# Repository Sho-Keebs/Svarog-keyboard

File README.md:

## ⚠ Notice

This project is no longer under active developement. If you want to work on this, please contact me @ [echelon.div@gmail.com](mailto:echelon.div@gmail.com).

# Svarog-keyboard

This is my first attempt to make mechanical keyboard. It was supposed to look little bit retro, and have as many additional keys as possible, without taking a lot of space. Additionaly it has customizable and optional sidepanels (Numerical and Navigational).

# License and availability

The whole project is released under GNU GPL v3. What does it mean? You can get fabrication files completely free of charge, modify the source files of keyboard, and even fabricate and sell it without me knowing it. What’s the catch then? You have to have few things in mind:
- There is no liability or warranty from my side that the keyboard is working (especially in current state),
- If you want to fork my project you have to use the same license.

# Firmware

The goal is to use QMK. BUT Board is untested, no one built it yet. So obviously there is no working QMK configuration for it. You might get it working while using Discipline 65 config, but you won’t be able to get all keys working (if any), as pins on ATMega32A microcontroller are wired differently between these two keyboards.

# Supported Layouts

1. Split and 2u `Backspace`,
2. 6.25u and 7u `Spacebar`
3. ISO and ANSI `Return`
4. Split and 2.25u `Left Shift`
5. Split and 2.75 `Full Shift`
6. Split and 2u `Enter (NumPad)`
7. Split and 2u `0 / Ins`
8. Split and 2u `+`

# Parts

|Part|Amount|Picture|
|---|---|---|
|ATMega32A-PU|1||
|DIP-40 15.24mm Socket|1||
|MCP23017-E/SP|3||
|DIP-28 7.62mm Socket|3||
|MX Style 5-pin Switch|124||
|Diodes 1N4148|124||
|ISP Header 02x03 2.54mm|1||
|16 MHz Crystal|1||
|6mm Push Buttons|2||
|LED 3.0mm|7||
|Electrolictic Capacitor 4.7uF|1||
|Ceramic Capacitor 22pF|2||
|Ceramic Capacitor 0.1uF|2||
|Zener Diode 3.6V|2||
|Polyfuse 500mA|1||
|Resistor 1.5k Ohm|8||
|Resistor 10k Ohm|3||
|Resistor 5.1k Ohm|2||
|Resistor 75 Ohm|2||

# Pre-Release
So as for now, I’ve published pre-release fabrication files for anyone who want to try to build and test it in it’s current form.

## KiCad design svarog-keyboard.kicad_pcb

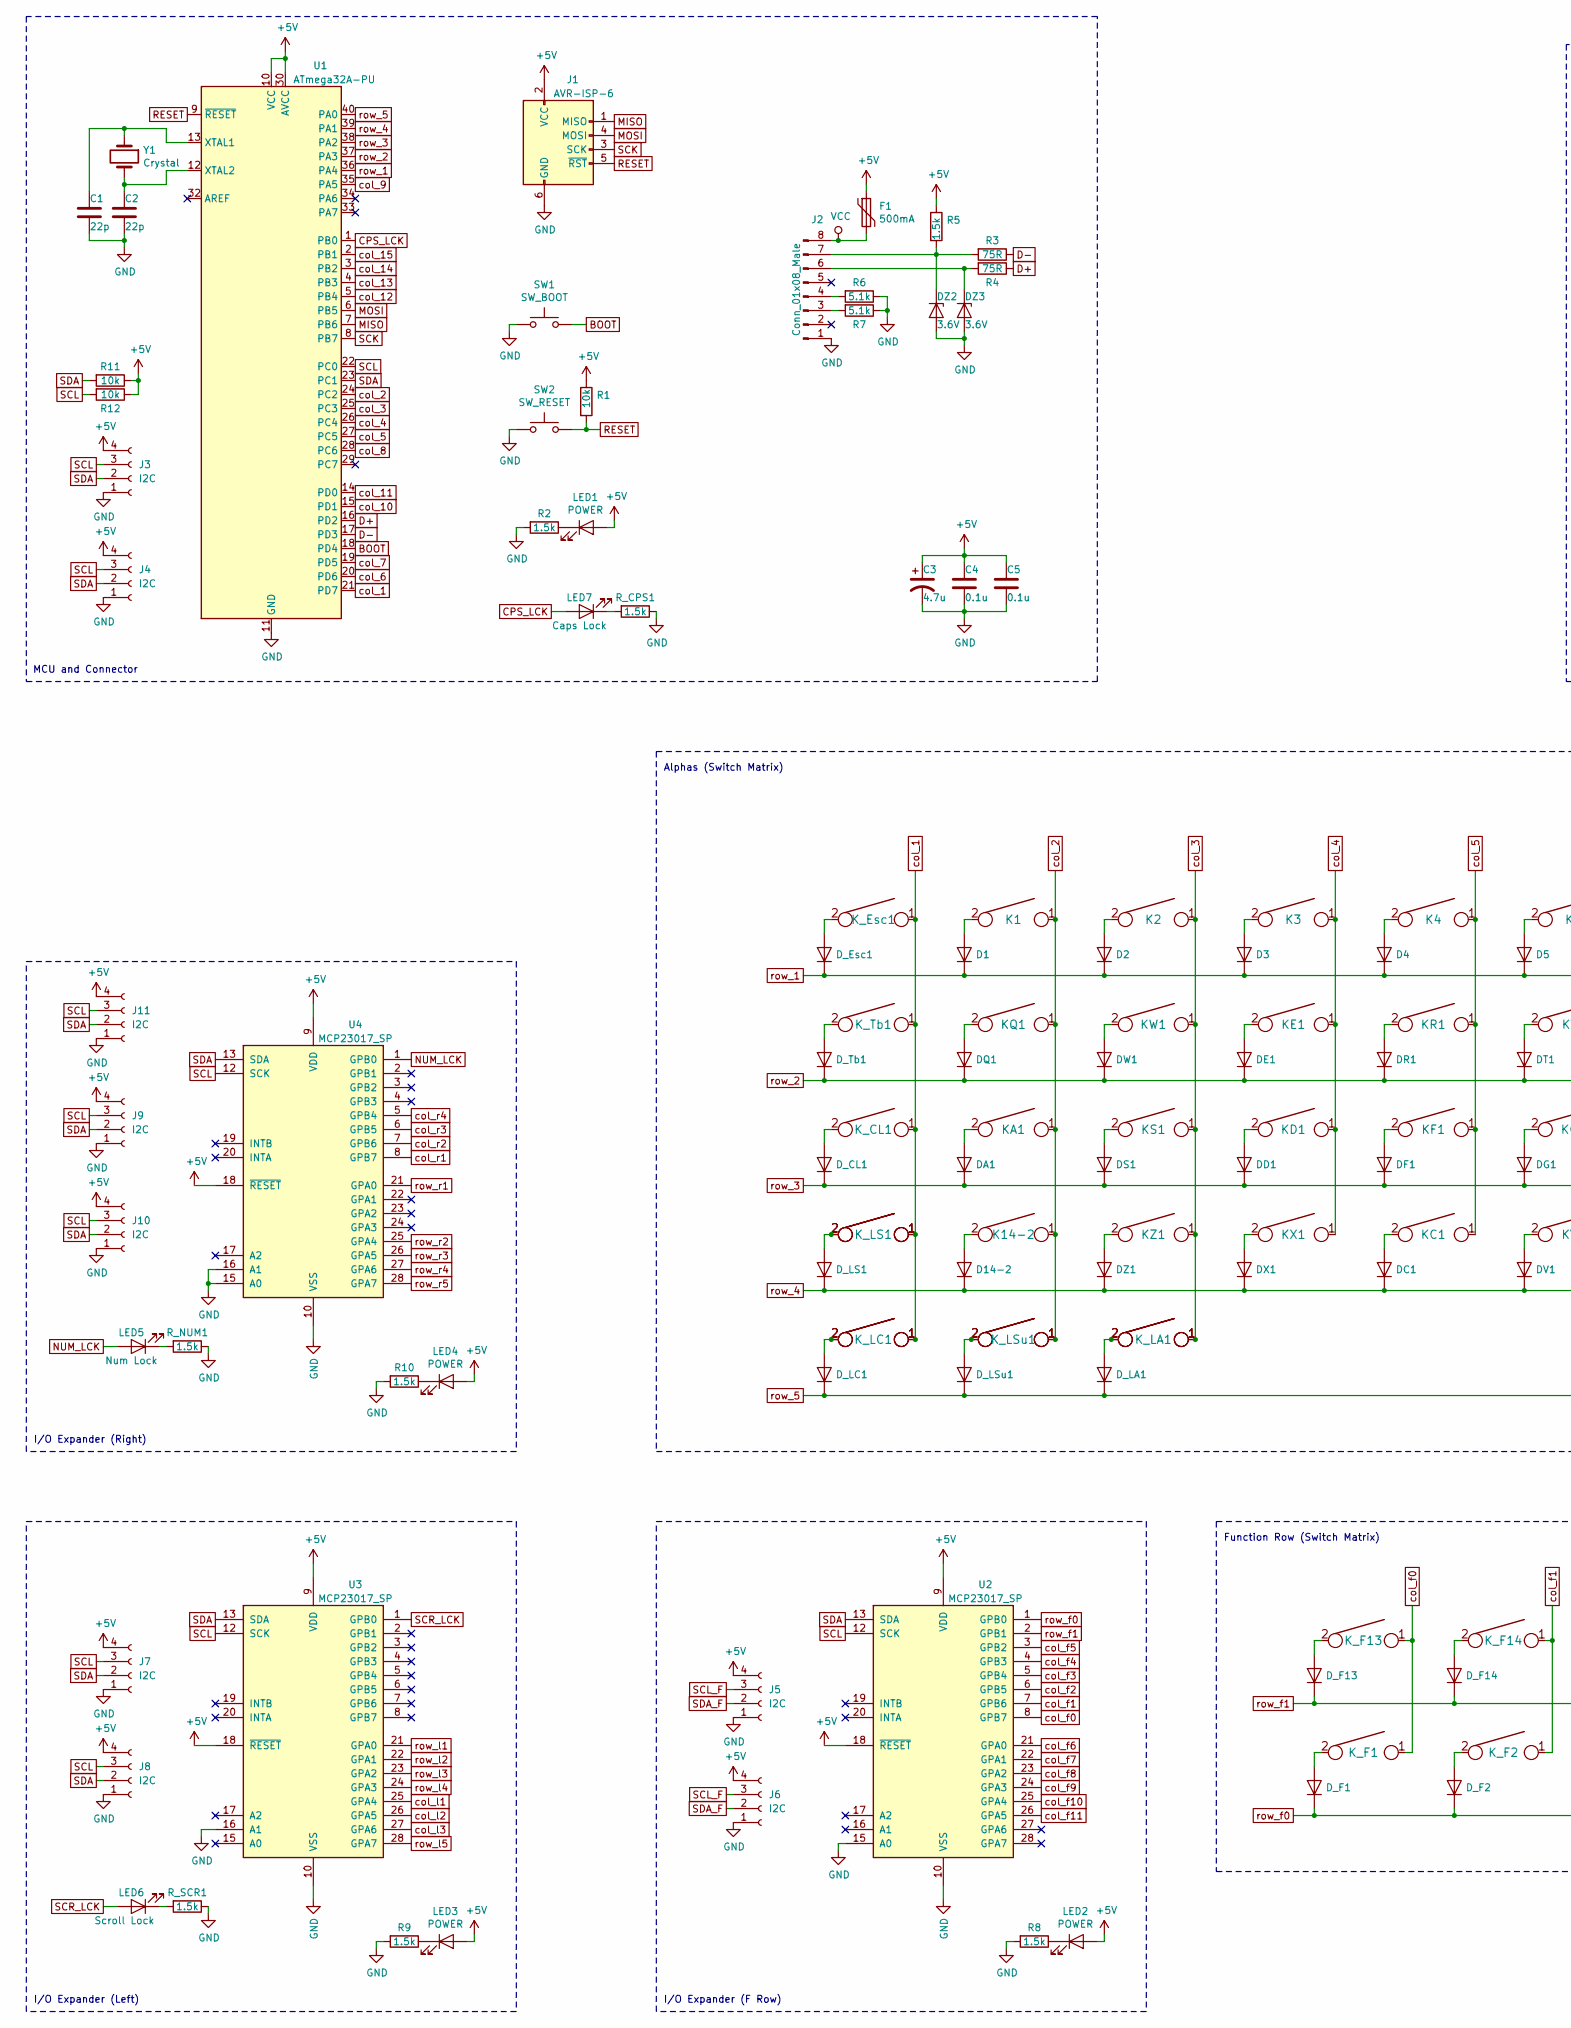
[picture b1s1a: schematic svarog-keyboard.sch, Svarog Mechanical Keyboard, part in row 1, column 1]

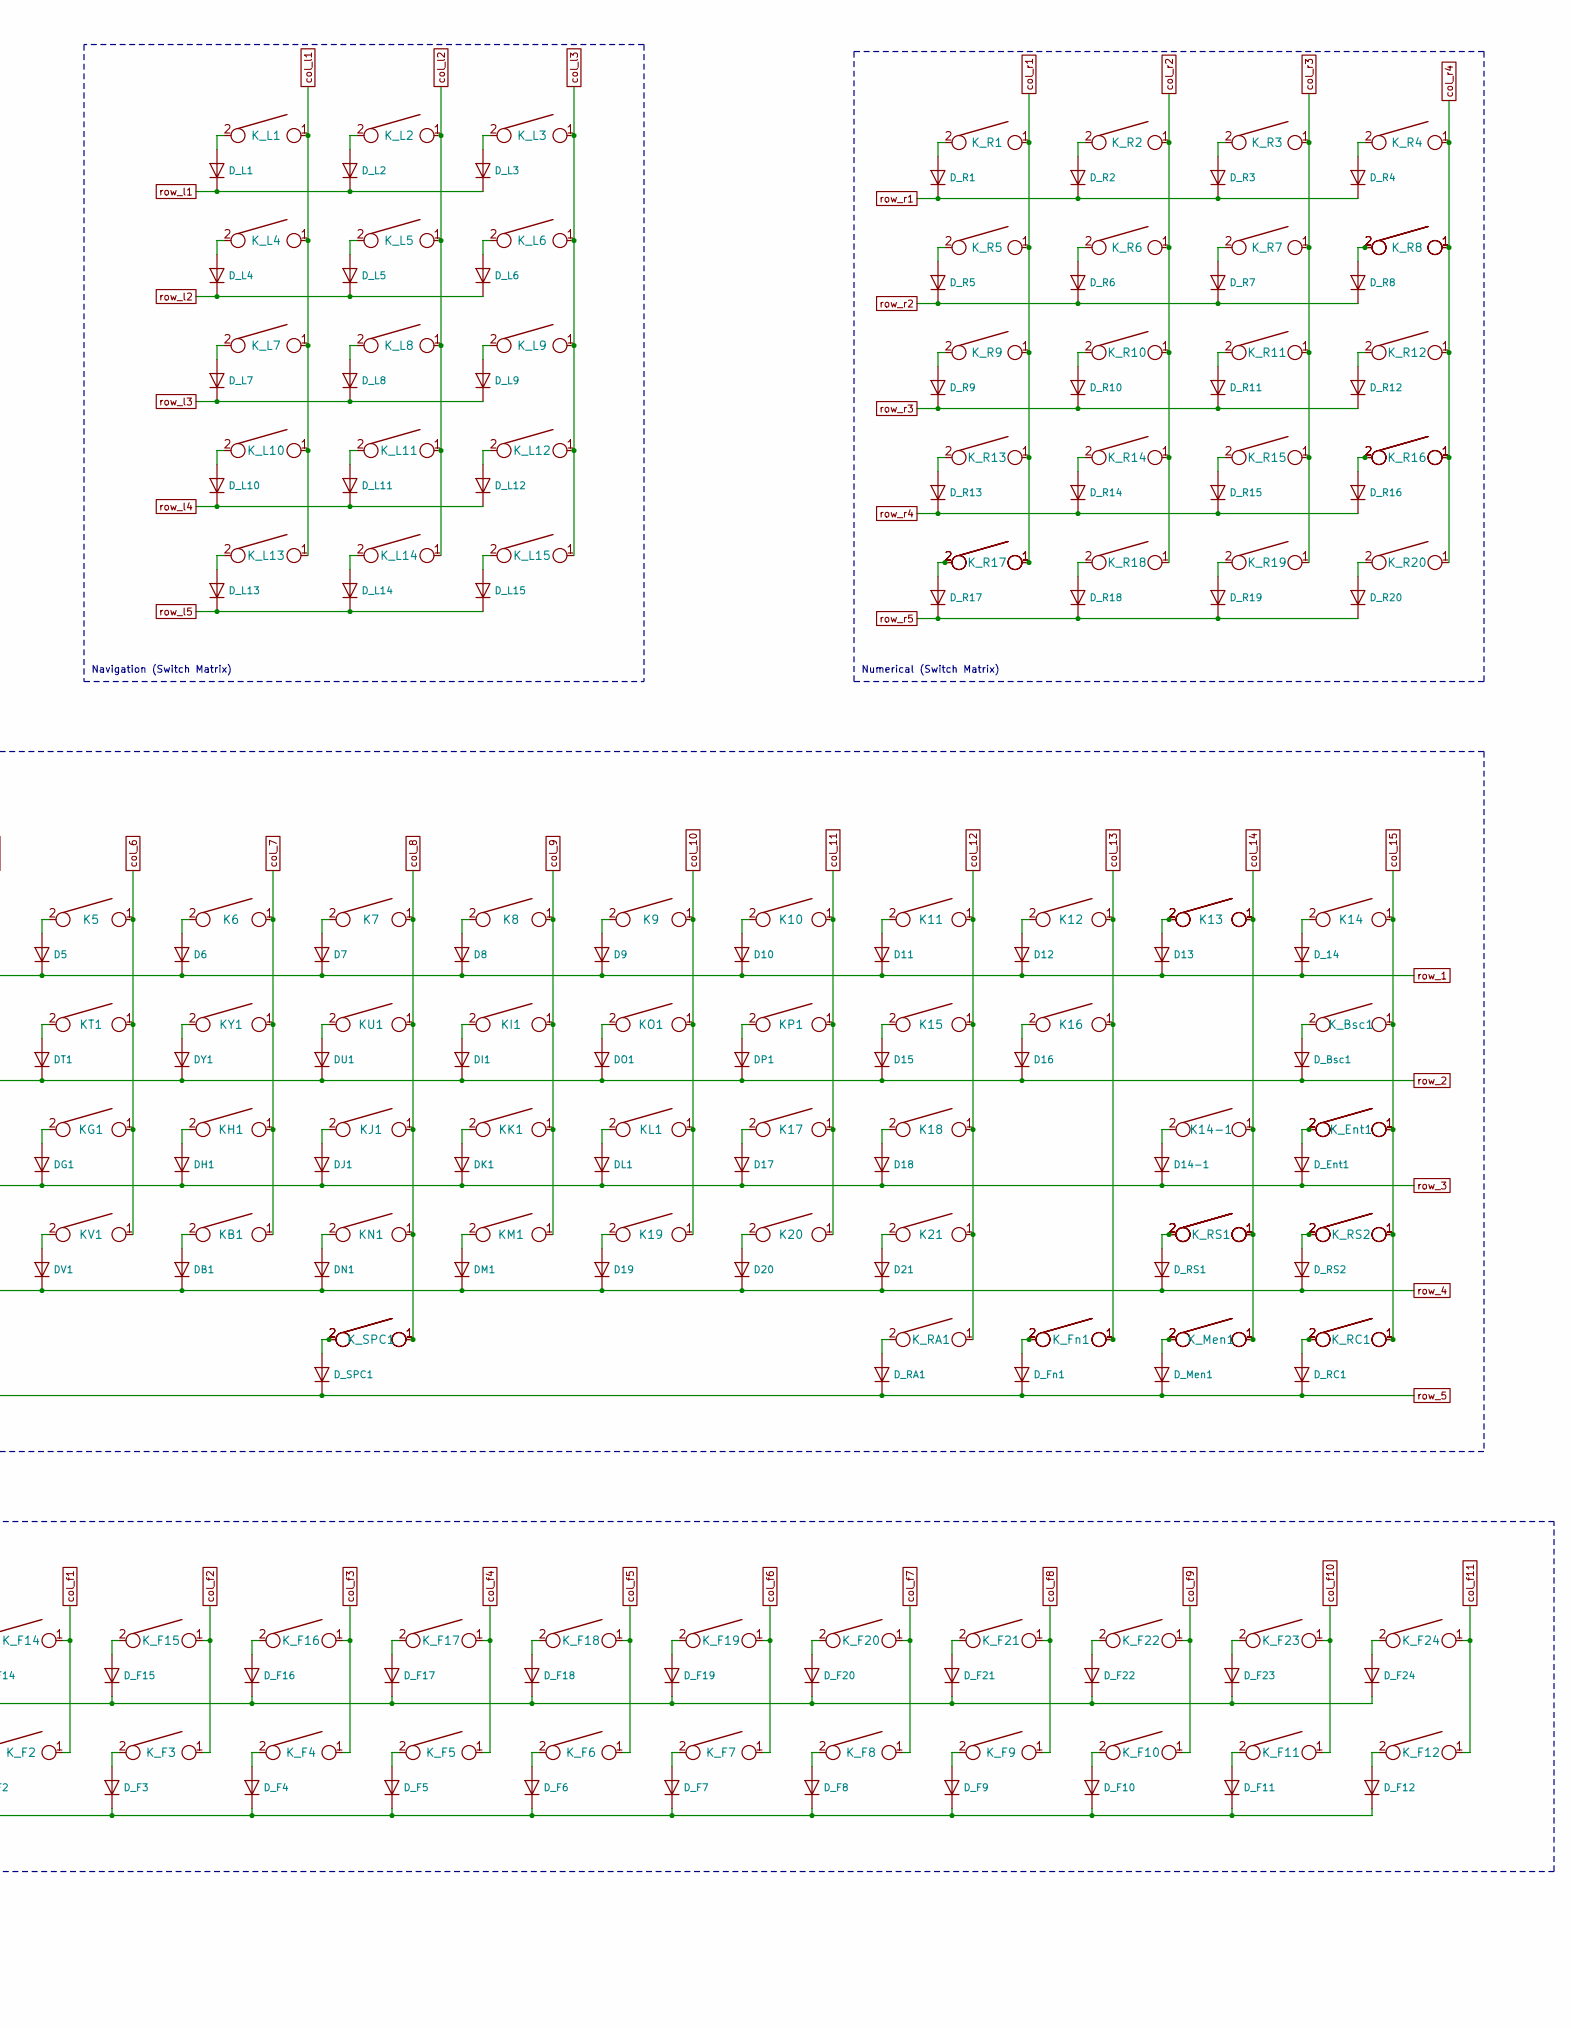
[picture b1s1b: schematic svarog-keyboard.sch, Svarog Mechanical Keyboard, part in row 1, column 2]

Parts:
C1: 22p; C_Disc_D3.4mm_W2.1mm_P2.50mm
C2: 22p; C_Disc_D3.8mm_W2.6mm_P2.50mm
C3: 4.7u; CP_Radial_D4.0mm_P1.50mm
C4, C5: 0.1u; C_Disc_D3.8mm_W2.6mm_P2.50mm
D1, D2, D3, D4, D5, D6, D7, D8, D9, D10, D11, D12, D13, D14-1, D14-2, D15, D16, D17, D18, D19, D20, D21: D; D_DO-35_SOD27_P7.62mm_Horizontal
DA1: D; D_DO-35_SOD27_P7.62mm_Horizontal
DB1: D; D_DO-35_SOD27_P7.62mm_Horizontal
DC1: D; D_DO-35_SOD27_P7.62mm_Horizontal
DD1: D; D_DO-35_SOD27_P7.62mm_Horizontal
DE1: D; D_DO-35_SOD27_P7.62mm_Horizontal
DF1: D; D_DO-35_SOD27_P7.62mm_Horizontal
DG1: D; D_DO-35_SOD27_P7.62mm_Horizontal
DH1: D; D_DO-35_SOD27_P7.62mm_Horizontal
DI1: D; D_DO-35_SOD27_P7.62mm_Horizontal
DJ1: D; D_DO-35_SOD27_P7.62mm_Horizontal
DK1: D; D_DO-35_SOD27_P7.62mm_Horizontal
DL1: D; D_DO-35_SOD27_P7.62mm_Horizontal
DM1: D; D_DO-35_SOD27_P7.62mm_Horizontal
DN1: D; D_DO-35_SOD27_P7.62mm_Horizontal
DO1: D; D_DO-35_SOD27_P7.62mm_Horizontal
DP1: D; D_DO-35_SOD27_P7.62mm_Horizontal
DQ1: D; D_DO-35_SOD27_P7.62mm_Horizontal
DR1: D; D_DO-35_SOD27_P7.62mm_Horizontal
DS1: D; D_DO-35_SOD27_P7.62mm_Horizontal
DT1: D; D_DO-35_SOD27_P7.62mm_Horizontal
DU1: D; D_DO-35_SOD27_P7.62mm_Horizontal
DV1: D; D_DO-35_SOD27_P7.62mm_Horizontal
DW1: D; D_DO-35_SOD27_P7.62mm_Horizontal
DX1: D; D_DO-35_SOD27_P7.62mm_Horizontal
DY1: D; D_DO-35_SOD27_P7.62mm_Horizontal
DZ1: D; D_DO-35_SOD27_P7.62mm_Horizontal
DZ2, DZ3: 3.6V; D_DO-35_SOD27_P7.62mm_Horizontal
D_14: D; D_DO-35_SOD27_P7.62mm_Horizontal
D_Bsc1: D; D_DO-35_SOD27_P7.62mm_Horizontal
D_CL1: D; D_DO-35_SOD27_P7.62mm_Horizontal
D_Ent1: D; D_DO-35_SOD27_P7.62mm_Horizontal
D_Esc1: D; D_DO-35_SOD27_P7.62mm_Horizontal
D_F1, D_F2, D_F3, D_F4, D_F5, D_F6, D_F7, D_F8, D_F9, D_F10, D_F11, D_F12, D_F13, D_F14, D_F15, D_F16, D_F17, D_F18, D_F19, D_F20, D_F21, D_F22, D_F23, D_F24: D; D_DO-35_SOD27_P7.62mm_Horizontal
D_Fn1: D; D_DO-35_SOD27_P7.62mm_Horizontal
D_L1, D_L2, D_L3, D_L4, D_L5, D_L6, D_L7, D_L8, D_L9, D_L10, D_L11, D_L12, D_L13, D_L14, D_L15: D; D_DO-35_SOD27_P7.62mm_Horizontal
D_LA1: D; D_DO-35_SOD27_P7.62mm_Horizontal
D_LC1: D; D_DO-35_SOD27_P7.62mm_Horizontal
D_LS1: D; D_DO-35_SOD27_P7.62mm_Horizontal
D_LSu1: D; D_DO-35_SOD27_P7.62mm_Horizontal
D_Men1: D; D_DO-35_SOD27_P7.62mm_Horizontal
D_R1, D_R2, D_R3, D_R4, D_R5, D_R6, D_R7, D_R8, D_R9, D_R10, D_R11, D_R12, D_R13, D_R14, D_R15, D_R16, D_R17, D_R18, D_R19, D_R20: D; D_DO-35_SOD27_P7.62mm_Horizontal
D_RA1: D; D_DO-35_SOD27_P7.62mm_Horizontal
D_RC1: D; D_DO-35_SOD27_P7.62mm_Horizontal
D_RS1, D_RS2: D; D_DO-35_SOD27_P7.62mm_Horizontal
D_SPC1: D; D_DO-35_SOD27_P7.62mm_Horizontal
D_Tb1: D; D_DO-35_SOD27_P7.62mm_Horizontal
F1: 500mA; C_Disc_D9.0mm_W5.0mm_P10.00mm
J1: AVR-ISP-6; PinHeader_2x03_P2.54mm_Vertical
J2: Conn_01x08_Male; PinHeader_1x08_P2.54mm_Vertical
J3, J4, J5, J6, J7, J8, J9, J10, J11: I2C; PinHeader_1x04_P2.54mm_Vertical
K1, K2, K3, K4, K5, K6, K7, K8, K9, K10, K11, K12, K13, K14, K14-1, K14-2, K15, K16, K17, K18, K19, K20, K21: KEYSW; SW_Cherry_MX_1.00u_PCB
K13-1: KEYSW; SW_Cherry_MX_2.00u_PCB
KA1: KEYSW; SW_Cherry_MX_1.00u_PCB
KB1: KEYSW; SW_Cherry_MX_1.00u_PCB
KC1: KEYSW; SW_Cherry_MX_1.00u_PCB
KD1: KEYSW; SW_Cherry_MX_1.00u_PCB
KE1: KEYSW; SW_Cherry_MX_1.00u_PCB
KF1: KEYSW; SW_Cherry_MX_1.00u_PCB
KG1: KEYSW; SW_Cherry_MX_1.00u_PCB
KH1: KEYSW; SW_Cherry_MX_1.00u_PCB
KI1: KEYSW; SW_Cherry_MX_1.00u_PCB
KJ1: KEYSW; SW_Cherry_MX_1.00u_PCB
KK1: KEYSW; SW_Cherry_MX_1.00u_PCB
KL1: KEYSW; SW_Cherry_MX_1.00u_PCB
KM1: KEYSW; SW_Cherry_MX_1.00u_PCB
KN1: KEYSW; SW_Cherry_MX_1.00u_PCB
KO1: KEYSW; SW_Cherry_MX_1.00u_PCB
KP1: KEYSW; SW_Cherry_MX_1.00u_PCB
KQ1: KEYSW; SW_Cherry_MX_1.00u_PCB
KR1: KEYSW; SW_Cherry_MX_1.00u_PCB
KS1: KEYSW; SW_Cherry_MX_1.00u_PCB
KT1: KEYSW; SW_Cherry_MX_1.00u_PCB
KU1: KEYSW; SW_Cherry_MX_1.00u_PCB
KV1: KEYSW; SW_Cherry_MX_1.00u_PCB
KW1: KEYSW; SW_Cherry_MX_1.00u_PCB
KX1: KEYSW; SW_Cherry_MX_1.00u_PCB
KY1: KEYSW; SW_Cherry_MX_1.00u_PCB
KZ1: KEYSW; SW_Cherry_MX_1.00u_PCB
K_Bsc1: KEYSW; SW_Cherry_MX_1.50u_PCB
K_CL1: KEYSW; SW_Cherry_MX_1.75u_PCB
K_Ent1: KEYSW; SW_Cherry_MX_2.25u_PCB
K_Ent-1: KEYSW; SW_Cherry_MX_ISOEnter_PCB
K_Esc1: KEYSW; SW_Cherry_MX_1.00u_PCB
K_F1, K_F2, K_F3, K_F4, K_F5, K_F6, K_F7, K_F8, K_F9, K_F10, K_F11, K_F12, K_F13, K_F14, K_F15, K_F16, K_F17, K_F18, K_F19, K_F20, K_F21, K_F22, K_F23, K_F24: KEYSW; SW_Cherry_MX_1.00u_PCB
K_Fn1: KEYSW; SW_Cherry_MX_1.25u_PCB
K_Fn1-1.5u1: KEYSW; SW_Cherry_MX_1.50u_PCB
K_L1, K_L2, K_L3, K_L4, K_L5, K_L6, K_L7, K_L8, K_L9, K_L10, K_L11, K_L12, K_L13, K_L14, K_L15: KEYSW; SW_Cherry_MX_1.00u_PCB
K_LA1: KEYSW; SW_Cherry_MX_1.25u_PCB
K_LA2-1.5u1: KEYSW; SW_Cherry_MX_1.50u_PCB
K_LC1: KEYSW; SW_Cherry_MX_1.25u_PCB
K_LC2-1.5u1: KEYSW; SW_Cherry_MX_1.50u_PCB
K_LS1: KEYSW; SW_Cherry_MX_2.25u_PCB
K_LS-1: KEYSW; SW_Cherry_MX_1.25u_PCB
K_LSu1: KEYSW; SW_Cherry_MX_1.25u_PCB
K_LSu2-1u1: KEYSW; SW_Cherry_MX_1.00u_PCB
K_Men1: KEYSW; SW_Cherry_MX_1.25u_PCB
K_Men1-1u1: KEYSW; SW_Cherry_MX_1.00u_PCB
K_R1, K_R2, K_R3, K_R4, K_R5, K_R6, K_R7, K_R8-1, K_R9, K_R10, K_R11, K_R12, K_R13, K_R14, K_R15, K_R16-1, K_R17-1, K_R18, K_R19, K_R20: KEYSW; SW_Cherry_MX_1.00u_PCB
K_R8, K_R16: KEYSW; SW_Cherry_MX_2.00u_Vertical_PCB
K_R17: KEYSW; SW_Cherry_MX_2.00u_PCB
K_RA1: KEYSW; SW_Cherry_MX_1.25u_PCB
K_RC1: KEYSW; SW_Cherry_MX_1.25u_PCB
K_RC2-1.5u1: KEYSW; SW_Cherry_MX_1.50u_PCB
K_RS1: KEYSW; SW_Cherry_MX_2.75u_PCB
K_RS1-1.75u1, K_RS2-1.75u1: KEYSW; SW_Cherry_MX_1.75u_PCB
K_RS1-1u1, K_RS2: KEYSW; SW_Cherry_MX_1.00u_PCB
K_SPC1: KEYSW; SW_Cherry_MX_6.25u_PCB
K_SPC2-7u1: KEYSW; MXOnly-7U-NoLED
K_Tb1: KEYSW; SW_Cherry_MX_1.50u_PCB
LED1, LED2, LED3, LED4: POWER; LED_D3.0mm
LED5: Num Lock; LED_D3.0mm
LED6: Scroll Lock; LED_D3.0mm
LED7: Caps Lock; LED_D3.0mm
R1, R11, R12: 10k; R_Axial_DIN0207_L6.3mm_D2.5mm_P7.62mm_Horizontal
R2, R5, R8, R9, R10: 1.5k; R_Axial_DIN0207_L6.3mm_D2.5mm_P7.62mm_Horizontal
R3, R4: 75R; R_Axial_DIN0207_L6.3mm_D2.5mm_P7.62mm_Horizontal
R6, R7: 5.1k; R_Axial_DIN0207_L6.3mm_D2.5mm_P7.62mm_Horizontal
R_CPS1: 1.5k; R_Axial_DIN0207_L6.3mm_D2.5mm_P7.62mm_Horizontal
R_NUM1: 1.5k; R_Axial_DIN0207_L6.3mm_D2.5mm_P7.62mm_Horizontal
R_SCR1: 1.5k; R_Axial_DIN0207_L6.3mm_D2.5mm_P7.62mm_Horizontal
SW1: SW_BOOT; SW_PUSH_6mm
SW2: SW_RESET; SW_PUSH_6mm
U1: ATmega32A-PU; DIP-40_W15.24mm_Socket
U2, U3, U4: MCP23017_SP; DIP-28_W7.62mm_Socket
Y1: Crystal; Crystal_HC49-4H_Vertical

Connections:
+5V: C3.1, C4.1, C5.1, F1.1, J1.2 (VCC), J3.4, J4.4, J5.4, J6.4, J7.4, J8.4, J9.4, J10.4, J11.4, LED1.2 (A), LED2.2 (A), LED3.2 (A), LED4.2 (A), R1.1, R5.1, R11.1, R12.1, U1.10 (VCC), U1.30 (AVCC), U2.9 (VDD), U2.18 (~RESET~), U3.9 (VDD), U3.18 (~RESET~), U4.9 (VDD), U4.18 (~RESET~)
BOOT: SW1.2, U1.18 (PD4)
CPS_LCK: LED7.2 (A), U1.1 (PB0)
D+: R4.1, U1.16 (PD2)
D-: R3.1, U1.17 (PD3)
GND: C1.2, C2.2, C3.2, C4.2, C5.2, DZ2.2 (A), DZ3.2 (A), J1.6 (GND), J2.1, J3.1, J4.1, J5.1, J6.1, J7.1, J8.1, J9.1, J10.1, J11.1, R2.2, R6.1, R7.1, R8.2, R9.2, R10.2, R_CPS1.1, R_NUM1.1, R_SCR1.1, SW1.1, SW2.1, U1.11 (GND), U1.31 (GND), U2.10 (VSS), U2.15 (A0), U3.10 (VSS), U3.16 (A1), U4.10 (VSS), U4.15 (A0), U4.16 (A1)
MISO: J1.1 (MISO), U1.7 (PB6)
MOSI: J1.4 (MOSI), U1.6 (PB5)
NUM_LCK: LED5.2 (A), U4.1 (GPB0)
unnamed: C1.1, U1.13 (XTAL1), Y1.1
unnamed: C2.1, U1.12 (XTAL2), Y1.2
unnamed: D1.2 (A), K1.2
unnamed: D2.2 (A), K2.2
unnamed: D3.2 (A), K3.2
unnamed: D4.2 (A), K4.2
unnamed: D5.2 (A), K5.2
unnamed: D6.2 (A), K6.2
unnamed: D7.2 (A), K7.2
unnamed: D8.2 (A), K8.2
unnamed: D9.2 (A), K9.2
unnamed: D10.2 (A), K10.2
unnamed: D11.2 (A), K11.2
unnamed: D12.2 (A), K12.2
unnamed: D13.2 (A), K13.2, K13-1.2
unnamed: D14-1.2 (A), K14-1.2
unnamed: D14-2.2 (A), K14-2.2
unnamed: D15.2 (A), K15.2
unnamed: D16.2 (A), K16.2
unnamed: D17.2 (A), K17.2
unnamed: D18.2 (A), K18.2
unnamed: D19.2 (A), K19.2
unnamed: D20.2 (A), K20.2
unnamed: D21.2 (A), K21.2
unnamed: DA1.2 (A), KA1.2
unnamed: DB1.2 (A), KB1.2
unnamed: DC1.2 (A), KC1.2
unnamed: DD1.2 (A), KD1.2
unnamed: DE1.2 (A), KE1.2
unnamed: DF1.2 (A), KF1.2
unnamed: DG1.2 (A), KG1.2
unnamed: DH1.2 (A), KH1.2
unnamed: DI1.2 (A), KI1.2
unnamed: DJ1.2 (A), KJ1.2
unnamed: DK1.2 (A), KK1.2
unnamed: DL1.2 (A), KL1.2
unnamed: DM1.2 (A), KM1.2
unnamed: DN1.2 (A), KN1.2
unnamed: DO1.2 (A), KO1.2
unnamed: DP1.2 (A), KP1.2
unnamed: DQ1.2 (A), KQ1.2
unnamed: DR1.2 (A), KR1.2
unnamed: DS1.2 (A), KS1.2
unnamed: DT1.2 (A), KT1.2
unnamed: DU1.2 (A), KU1.2
unnamed: DV1.2 (A), KV1.2
unnamed: DW1.2 (A), KW1.2
unnamed: DX1.2 (A), KX1.2
unnamed: DY1.2 (A), KY1.2
unnamed: DZ1.2 (A), KZ1.2
unnamed: DZ2.1 (K), J2.7, R3.2, R5.2
unnamed: DZ3.1 (K), J2.6, R4.2
unnamed: D_14.2 (A), K14.2
unnamed: D_Bsc1.2 (A), K_Bsc1.2
unnamed: D_CL1.2 (A), K_CL1.2
unnamed: D_Ent1.2 (A), K_Ent1.2, K_Ent-1.2
unnamed: D_Esc1.2 (A), K_Esc1.2
unnamed: D_F1.2 (A), K_F1.2
unnamed: D_F2.2 (A), K_F2.2
unnamed: D_F3.2 (A), K_F3.2
unnamed: D_F4.2 (A), K_F4.2
unnamed: D_F5.2 (A), K_F5.2
unnamed: D_F6.2 (A), K_F6.2
unnamed: D_F7.2 (A), K_F7.2
unnamed: D_F8.2 (A), K_F8.2
unnamed: D_F9.2 (A), K_F9.2
unnamed: D_F10.2 (A), K_F10.2
unnamed: D_F11.2 (A), K_F11.2
unnamed: D_F12.2 (A), K_F12.2
unnamed: D_F13.2 (A), K_F13.2
unnamed: D_F14.2 (A), K_F14.2
unnamed: D_F15.2 (A), K_F15.2
unnamed: D_F16.2 (A), K_F16.2
unnamed: D_F17.2 (A), K_F17.2
unnamed: D_F18.2 (A), K_F18.2
unnamed: D_F19.2 (A), K_F19.2
unnamed: D_F20.2 (A), K_F20.2
unnamed: D_F21.2 (A), K_F21.2
unnamed: D_F22.2 (A), K_F22.2
unnamed: D_F23.2 (A), K_F23.2
unnamed: D_F24.2 (A), K_F24.2
unnamed: D_Fn1.2 (A), K_Fn1.2, K_Fn1-1.5u1.2
unnamed: D_L1.2 (A), K_L1.2
unnamed: D_L2.2 (A), K_L2.2
unnamed: D_L3.2 (A), K_L3.2
unnamed: D_L4.2 (A), K_L4.2
unnamed: D_L5.2 (A), K_L5.2
unnamed: D_L6.2 (A), K_L6.2
unnamed: D_L7.2 (A), K_L7.2
unnamed: D_L8.2 (A), K_L8.2
unnamed: D_L9.2 (A), K_L9.2
unnamed: D_L10.2 (A), K_L10.2
unnamed: D_L11.2 (A), K_L11.2
unnamed: D_L12.2 (A), K_L12.2
unnamed: D_L13.2 (A), K_L13.2
unnamed: D_L14.2 (A), K_L14.2
unnamed: D_L15.2 (A), K_L15.2
unnamed: D_LA1.2 (A), K_LA1.2, K_LA2-1.5u1.2
unnamed: D_LC1.2 (A), K_LC1.2, K_LC2-1.5u1.2
unnamed: D_LS1.2 (A), K_LS1.2, K_LS-1.2
unnamed: D_LSu1.2 (A), K_LSu1.2, K_LSu2-1u1.2
unnamed: D_Men1.2 (A), K_Men1.2, K_Men1-1u1.2
unnamed: D_R1.2 (A), K_R1.2
unnamed: D_R2.2 (A), K_R2.2
unnamed: D_R3.2 (A), K_R3.2
unnamed: D_R4.2 (A), K_R4.2
unnamed: D_R5.2 (A), K_R5.2
unnamed: D_R6.2 (A), K_R6.2
unnamed: D_R7.2 (A), K_R7.2
unnamed: D_R8.2 (A), K_R8.2, K_R8-1.2
unnamed: D_R9.2 (A), K_R9.2
unnamed: D_R10.2 (A), K_R10.2
unnamed: D_R11.2 (A), K_R11.2
unnamed: D_R12.2 (A), K_R12.2
unnamed: D_R13.2 (A), K_R13.2
unnamed: D_R14.2 (A), K_R14.2
unnamed: D_R15.2 (A), K_R15.2
unnamed: D_R16.2 (A), K_R16.2, K_R16-1.2
unnamed: D_R17.2 (A), K_R17.2, K_R17-1.2
unnamed: D_R18.2 (A), K_R18.2
unnamed: D_R19.2 (A), K_R19.2
unnamed: D_R20.2 (A), K_R20.2
unnamed: D_RA1.2 (A), K_RA1.2
unnamed: D_RC1.2 (A), K_RC1.2, K_RC2-1.5u1.2
unnamed: D_RS1.2 (A), K_RS1.2, K_RS1-1.75u1.2, K_RS1-1u1.2
unnamed: D_RS2.2 (A), K_RS2.2, K_RS2-1.75u1.2
unnamed: D_SPC1.2 (A), K_SPC1.2, K_SPC2-7u1.2
unnamed: D_Tb1.2 (A), K_Tb1.2
unnamed: J2.3, R7.2
unnamed: J2.4, R6.2
unnamed: LED1.1 (K), R2.1
unnamed: LED2.1 (K), R8.1
unnamed: LED3.1 (K), R9.1
unnamed: LED4.1 (K), R10.1
unnamed: LED5.1 (K), R_NUM1.2
unnamed: LED6.1 (K), R_SCR1.2
unnamed: LED7.1 (K), R_CPS1.2
RESET: J1.5 (~RST), R1.2, SW2.2, U1.9 (~RESET)
SCK: J1.3 (SCK), U1.8 (PB7)
SCR_LCK: LED6.2 (A), U3.1 (GPB0)
VCC: F1.2, J2.8
col_1: K_CL1.1, K_Esc1.1, K_LC1.1, K_LC2-1.5u1.1, K_LS1.1, K_LS-1.1, K_Tb1.1, U1.21 (PD7)
col_2: K1.1, K14-2.1, KA1.1, KQ1.1, K_LSu1.1, K_LSu2-1u1.1, U1.24 (PC2)
col_3: K2.1, KS1.1, KW1.1, KZ1.1, K_LA1.1, K_LA2-1.5u1.1, U1.25 (PC3)
col_4: K3.1, KD1.1, KE1.1, KX1.1, U1.26 (PC4)
col_5: K4.1, KC1.1, KF1.1, KR1.1, U1.27 (PC5)
col_6: K5.1, KG1.1, KT1.1, KV1.1, U1.20 (PD6)
col_7: K6.1, KB1.1, KH1.1, KY1.1, U1.19 (PD5)
col_8: K7.1, KJ1.1, KN1.1, KU1.1, K_SPC1.1, K_SPC2-7u1.1, U1.28 (PC6)
col_9: K8.1, KI1.1, KK1.1, KM1.1, U1.35 (PA5)
col_10: K9.1, K19.1, KL1.1, KO1.1, U1.15 (PD1)
col_11: K10.1, K17.1, K20.1, KP1.1, U1.14 (PD0)
col_12: K11.1, K15.1, K18.1, K21.1, K_RA1.1, U1.5 (PB4)
col_13: K12.1, K16.1, K_Fn1.1, K_Fn1-1.5u1.1, U1.4 (PB3)
col_14: K13.1, K13-1.1, K14-1.1, K_Men1.1, K_Men1-1u1.1, K_RS1.1, K_RS1-1.75u1.1, K_RS1-1u1.1, U1.3 (PB2)
col_15: K14.1, K_Bsc1.1, K_Ent1.1, K_Ent-1.1, K_RC1.1, K_RC2-1.5u1.1, K_RS2.1, K_RS2-1.75u1.1, U1.2 (PB1)
col_f0: K_F1.1, K_F13.1, U2.8 (GPB7)
col_f1: K_F2.1, K_F14.1, U2.7 (GPB6)
col_f2: K_F3.1, K_F15.1, U2.6 (GPB5)
col_f3: K_F4.1, K_F16.1, U2.5 (GPB4)
col_f4: K_F5.1, K_F17.1, U2.4 (GPB3)
col_f5: K_F6.1, K_F18.1, U2.3 (GPB2)
col_f6: K_F7.1, K_F19.1, U2.21 (GPA0)
col_f7: K_F8.1, K_F20.1, U2.22 (GPA1)
col_f8: K_F9.1, K_F21.1, U2.23 (GPA2)
col_f9: K_F10.1, K_F22.1, U2.24 (GPA3)
col_f10: K_F11.1, K_F23.1, U2.25 (GPA4)
col_f11: K_F12.1, K_F24.1, U2.26 (GPA5)
col_l1: K_L1.1, K_L4.1, K_L7.1, K_L10.1, K_L13.1, U3.25 (GPA4)
col_l2: K_L2.1, K_L5.1, K_L8.1, K_L11.1, K_L14.1, U3.26 (GPA5)
col_l3: K_L3.1, K_L6.1, K_L9.1, K_L12.1, K_L15.1, U3.27 (GPA6)
col_r1: K_R1.1, K_R5.1, K_R9.1, K_R13.1, K_R17.1, K_R17-1.1, U4.8 (GPB7)
col_r2: K_R2.1, K_R6.1, K_R10.1, K_R14.1, K_R18.1, U4.7 (GPB6)
col_r3: K_R3.1, K_R7.1, K_R11.1, K_R15.1, K_R19.1, U4.6 (GPB5)
col_r4: K_R4.1, K_R8.1, K_R8-1.1, K_R12.1, K_R16.1, K_R16-1.1, K_R20.1, U4.5 (GPB4)
row_1: D1.1 (K), D2.1 (K), D3.1 (K), D4.1 (K), D5.1 (K), D6.1 (K), D7.1 (K), D8.1 (K), D9.1 (K), D10.1 (K), D11.1 (K), D12.1 (K), D13.1 (K), D_14.1 (K), D_Esc1.1 (K), U1.36 (PA4)
row_2: D15.1 (K), D16.1 (K), DE1.1 (K), DI1.1 (K), DO1.1 (K), DP1.1 (K), DQ1.1 (K), DR1.1 (K), DT1.1 (K), DU1.1 (K), DW1.1 (K), DY1.1 (K), D_Bsc1.1 (K), D_Tb1.1 (K), U1.37 (PA3)
row_3: D14-1.1 (K), D17.1 (K), D18.1 (K), DA1.1 (K), DD1.1 (K), DF1.1 (K), DG1.1 (K), DH1.1 (K), DJ1.1 (K), DK1.1 (K), DL1.1 (K), DS1.1 (K), D_CL1.1 (K), D_Ent1.1 (K), U1.38 (PA2)
row_4: D14-2.1 (K), D19.1 (K), D20.1 (K), D21.1 (K), DB1.1 (K), DC1.1 (K), DM1.1 (K), DN1.1 (K), DV1.1 (K), DX1.1 (K), DZ1.1 (K), D_LS1.1 (K), D_RS1.1 (K), D_RS2.1 (K), U1.39 (PA1)
row_5: D_Fn1.1 (K), D_LA1.1 (K), D_LC1.1 (K), D_LSu1.1 (K), D_Men1.1 (K), D_RA1.1 (K), D_RC1.1 (K), D_SPC1.1 (K), U1.40 (PA0)
row_f0: D_F1.1 (K), D_F2.1 (K), D_F3.1 (K), D_F4.1 (K), D_F5.1 (K), D_F6.1 (K), D_F7.1 (K), D_F8.1 (K), D_F9.1 (K), D_F10.1 (K), D_F11.1 (K), D_F12.1 (K), U2.1 (GPB0)
row_f1: D_F13.1 (K), D_F14.1 (K), D_F15.1 (K), D_F16.1 (K), D_F17.1 (K), D_F18.1 (K), D_F19.1 (K), D_F20.1 (K), D_F21.1 (K), D_F22.1 (K), D_F23.1 (K), D_F24.1 (K), U2.2 (GPB1)
row_l1: D_L1.1 (K), D_L2.1 (K), D_L3.1 (K), U3.21 (GPA0)
row_l2: D_L4.1 (K), D_L5.1 (K), D_L6.1 (K), U3.22 (GPA1)
row_l3: D_L7.1 (K), D_L8.1 (K), D_L9.1 (K), U3.23 (GPA2)
row_l4: D_L10.1 (K), D_L11.1 (K), D_L12.1 (K), U3.24 (GPA3)
row_l5: D_L13.1 (K), D_L14.1 (K), D_L15.1 (K), U3.28 (GPA7)
row_r1: D_R1.1 (K), D_R2.1 (K), D_R3.1 (K), D_R4.1 (K), U4.21 (GPA0)
row_r2: D_R5.1 (K), D_R6.1 (K), D_R7.1 (K), D_R8.1 (K), U4.25 (GPA4)
row_r3: D_R9.1 (K), D_R10.1 (K), D_R11.1 (K), D_R12.1 (K), U4.26 (GPA5)
row_r4: D_R13.1 (K), D_R14.1 (K), D_R15.1 (K), D_R16.1 (K), U4.27 (GPA6)
row_r5: D_R17.1 (K), D_R18.1 (K), D_R19.1 (K), D_R20.1 (K), U4.28 (GPA7)

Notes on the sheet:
I/O Expander (F Row)
Function Row (Switch Matrix)
Alphas (Switch Matrix)
Numerical (Switch Matrix)
Navigation (Switch Matrix)
MCU and Connector
I/O Expander (Left)
I/O Expander (Right)

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
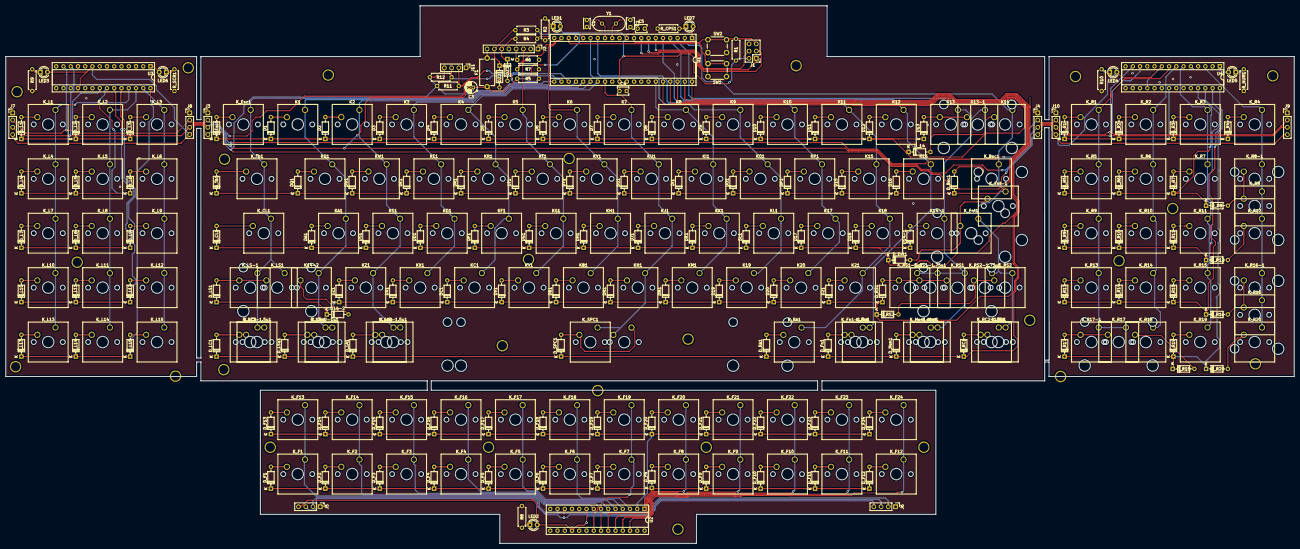
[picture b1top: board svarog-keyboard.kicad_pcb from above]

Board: 2 copper layers, 451.1 x 188.2 mm, 338 parts (0 on the bottom side), 205 nets.

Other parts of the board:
 : HOLE_M3
 #2,  #3,  #4,  #5,  #6,  #7,  #8,  #9,  #10,  #11,  #12,  #13,  #14,  #15,  #16,  #17,  #18,  #19,  #20,  #21,  #22,  #23,  #24,  #25,  #26: HOLE_M3

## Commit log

2019-12-09 Initail schematic
2019-12-09 Added Gitignore
2019-12-09 Improved Readme
2019-12-10 Added I/O expander
2020-01-06 Changed MCU from 32U4 to 32A, added new I/O expanders
2020-01-10 Starting adding footprints
2020-01-10 Started working on PCB
2020-01-11 Routing p.1
2020-01-12 Removed Traces, cleanup
2020-01-12 Wired [TODO] main matrix and [FULL] side matrixes
2020-01-12 Rev 0.1 [ALPHA] [UNTESTED]
2020-01-12 [PRERELEASE]
2020-01-13 [FIXED] unconnected row_f4
2020-01-13 Fix sizes
2020-01-13 Readme.md update
2020-01-14 Cleanup
